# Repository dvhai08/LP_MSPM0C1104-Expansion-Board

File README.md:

# LP_MSPM0C1104-Expansion-Board
MSPM0C1104 LaunchPad™ development kit for 24-MHz Arm® Cortex®-M0+ MCU

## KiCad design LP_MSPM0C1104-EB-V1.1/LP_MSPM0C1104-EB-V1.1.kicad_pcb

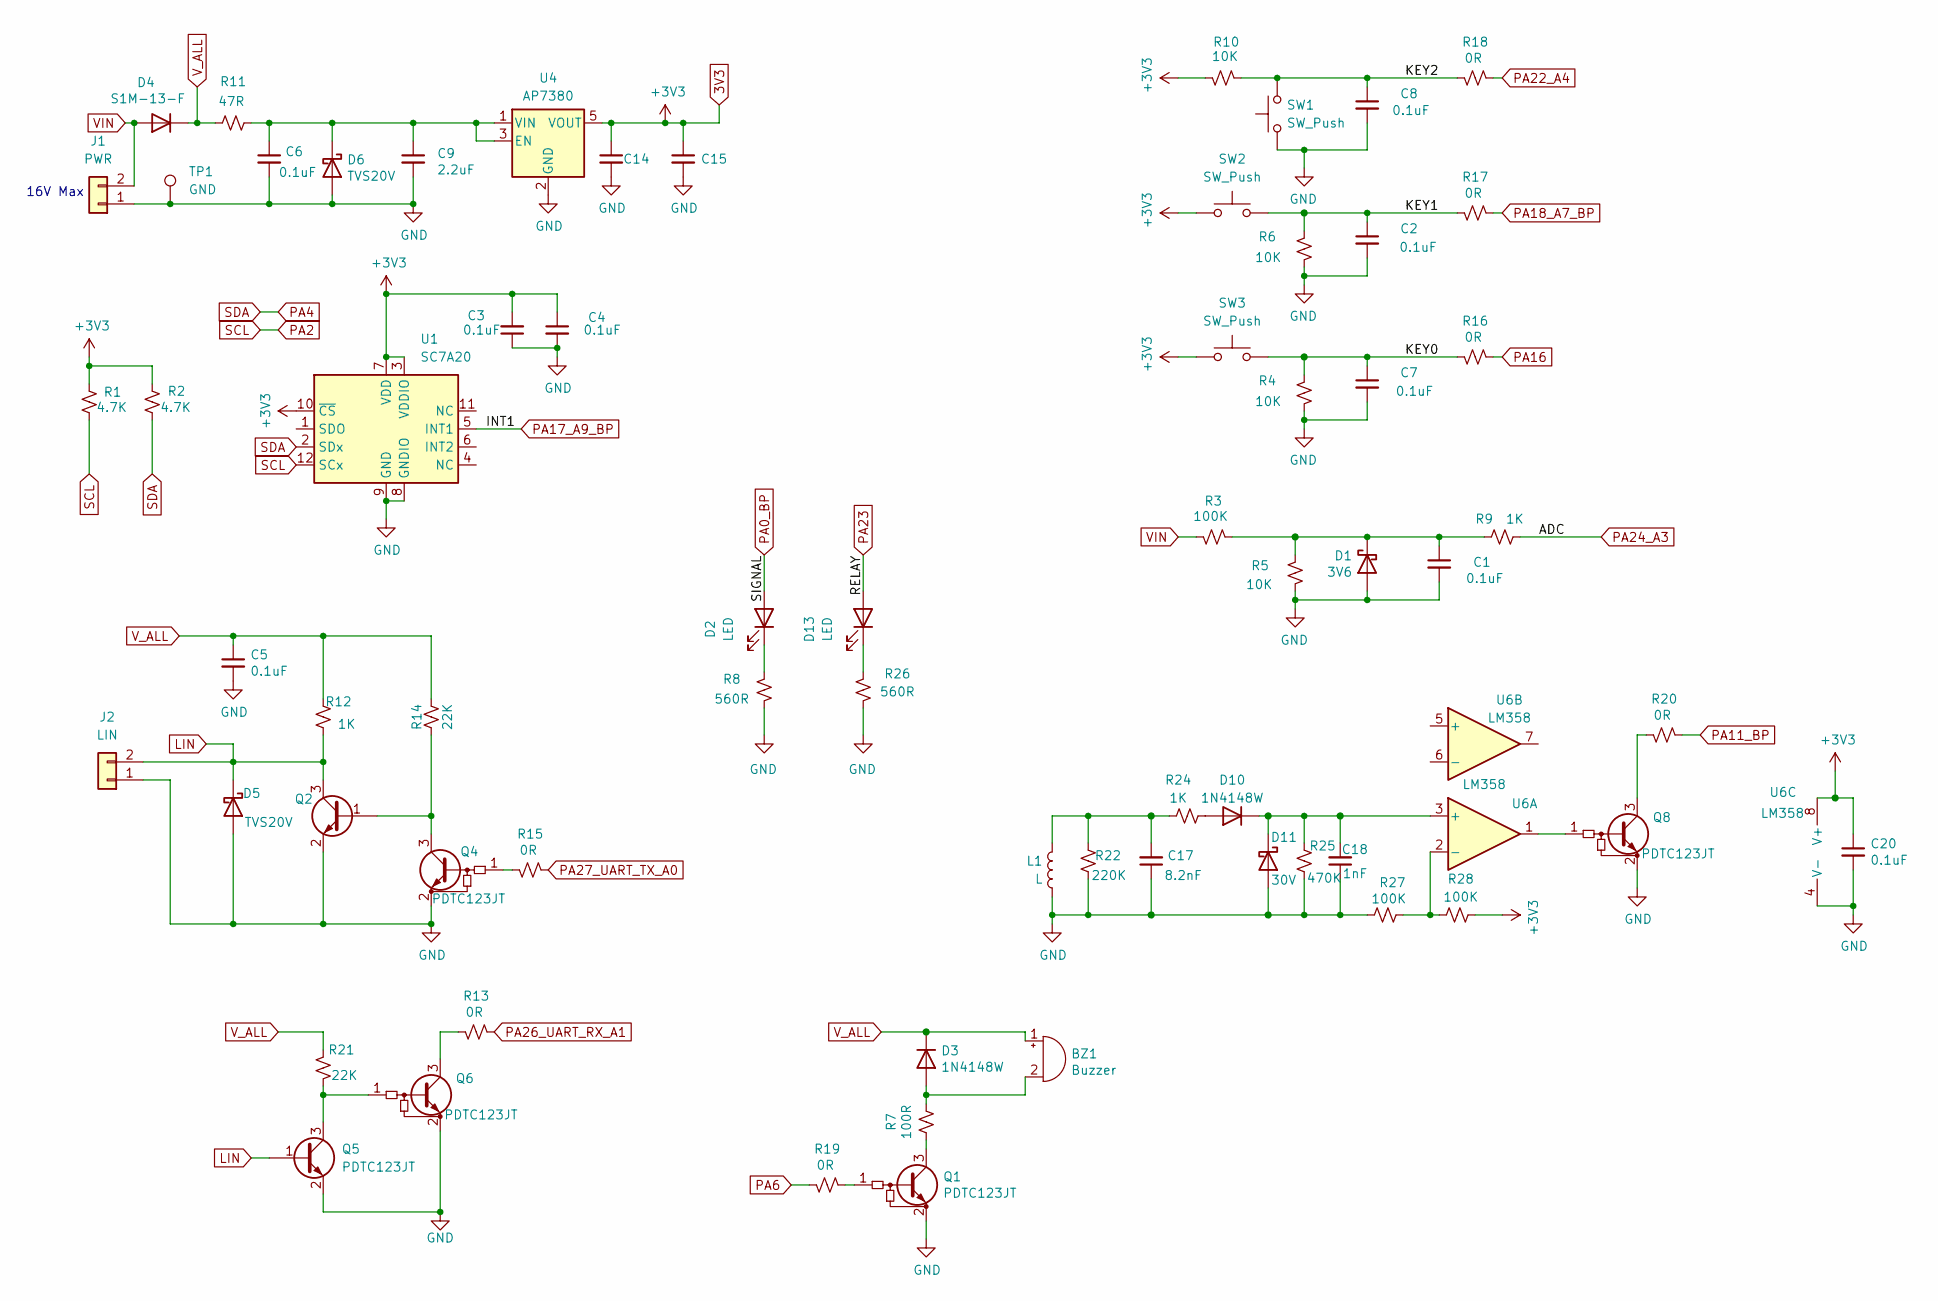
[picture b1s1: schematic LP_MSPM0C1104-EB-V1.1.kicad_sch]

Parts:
BZ1: Buzzer; BRT1209PF-06
C1, C2, C3, C4, C5, C6, C7, C8, C20: 0.1uF; C_0603_1608Metric
C9: 2.2uF; C_0603_1608Metric
C14: 0.1uF/50V; C_0402_1005Metric
C15: 4.7uF/10V; C_0603_1608Metric
C17: 8.2nF; C_0805_2012Metric
C18: 1nF; C_0603_1608Metric
D1: 3V6; D_SOD-323
D2, D13: LED; LED_0603_1608Metric
D3, D10: 1N4148W; D_SOD-123
D4: S1M-13-F; D_SMA
D5, D6: TVS20V; D_SMA
D11: 30V; D_SMA
J1: PWR; PinHeader_1x02_P2.54mm_Vertical
J2: LIN; PinHeader_1x02_P2.54mm_Vertical
L1: L; PinHeader_1x02_P2.54mm_Vertical
Q1, Q4, Q5, Q6, Q8: PDTC123JT; SOT-23
Q2: PBSS4041NT,215; SOT-23
R1, R2: 4.7K; R_0603_1608Metric
R3, R27, R28: 100K; R_0603_1608Metric
R4, R5, R6, R10: 10K; R_0603_1608Metric
R7: 100R; R_0805_2012Metric_Pad1.20x1.40mm_HandSolder
R8, R26: 560R; R_0603_1608Metric
R9, R24: 1K; R_0603_1608Metric
R11: 47R; R_1210_3225Metric
R12: 1K; R_1206_3216Metric
R13, R15, R16, R17, R18, R19, R20: 0R; R_0603_1608Metric
R14, R21: 22K; R_0603_1608Metric
R22: 220K; R_0603_1608Metric
R25: 470K; R_0603_1608Metric
SW1, SW2, SW3: SW_Push; SW_PUSH_6mm
TP1: GND; TestPoint_Pad_D1.0mm
U1: SC7A20; LGA-12_2x2mm_P0.5mm
U4: AP7380; SOT-23-5
U6: LM358; SOIC-8_3.9x4.9mm_P1.27mm

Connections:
3V3: C3.2, C4.1, C14.1, C15.1, C20.1, R1.1, R2.1, R10.1, R28.1, SW2.1, SW3.1, U1.3 (VDDIO), U1.7 (VDD), U1.10 (~CS), U4.5 (VOUT), U6.8 (V+); also elsewhere on the board
/KEY0: C7.1, R4.2, R16.2, SW3.2
/KEY1: C2.1, R6.2, R17.2, SW2.2
/KEY2: C8.1, R10.2, R18.2, SW1.2
GND: C1.2, C2.2, C3.1, C4.2, C5.2, C6.2, C7.2, C8.2, C9.2, C14.2, C15.2, C17.1, C18.1, C20.2, D1.2 (A), D5.2 (A), D6.2 (A), D11.2 (A), J1.1, J2.1, L1.2, Q1.2 (E), Q2.2 (E), Q4.2 (E), Q5.2 (E), Q6.2 (E), Q8.2 (E), R4.1, R5.1, R6.1, R8.1, R22.1, R25.1, R26.1, R27.1, SW1.1, TP1.1, U1.8 (GNDIO), U1.9 (GND), U4.2 (GND), U6.4 (V-); also elsewhere on the board
LIN: D5.1 (K), J2.2, Q2.3 (C), Q5.1 (B), R12.1
unnamed: BZ1.2 (+), D3.2 (A), R7.2
unnamed: C17.2, L1.1, R22.2, R24.2
unnamed: C1.1, D1.1 (K), R3.2, R5.2, R9.2
unnamed: D2.1 (K), R8.2
unnamed: C6.1, C9.1, D6.1 (K), R11.1, U4.1 (VIN), U4.3 (EN)
unnamed: D10.2 (A), R24.1
unnamed: C18.2, D10.1 (K), D11.1 (K), R25.2, U6.3 (+)
unnamed: D13.1 (K), R26.2
unnamed: Q1.1 (B), R19.1
unnamed: Q1.3 (C), R7.1
unnamed: Q2.1 (B), Q4.3 (C), R14.2
unnamed: Q4.1 (B), R15.2
unnamed: Q5.3 (C), Q6.1 (B), R21.1
unnamed: Q6.3 (C), R13.2
unnamed: Q8.1 (B), U6.1
unnamed: Q8.3 (C), R20.2
unnamed: R27.2, R28.2, U6.2 (-)
PA0_BP: D2.2 (A); also elsewhere on the board
PA2: R1.2, U1.12 (SCx); also elsewhere on the board
PA4: R2.2, U1.2 (SDx); also elsewhere on the board
PA6: R19.2; also elsewhere on the board
PA11_BP: R20.1; also elsewhere on the board
PA16: R16.1; also elsewhere on the board
PA17_A9_BP: U1.5 (INT1); also elsewhere on the board
PA18_A7_BP: R17.1; also elsewhere on the board
PA22_A4: R18.1; also elsewhere on the board
PA23: D13.2 (A); also elsewhere on the board
PA24_A3: R9.1; also elsewhere on the board
PA26_UART_RX_A1: R13.1; also elsewhere on the board
PA27_UART_TX_A0: R15.1; also elsewhere on the board
VIN: D4.2 (A), J1.2, R3.1
V_ALL: BZ1.1 (-), C5.1, D3.1 (K), D4.1 (K), R11.2, R12.2, R14.1, R21.2

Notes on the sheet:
16V Max

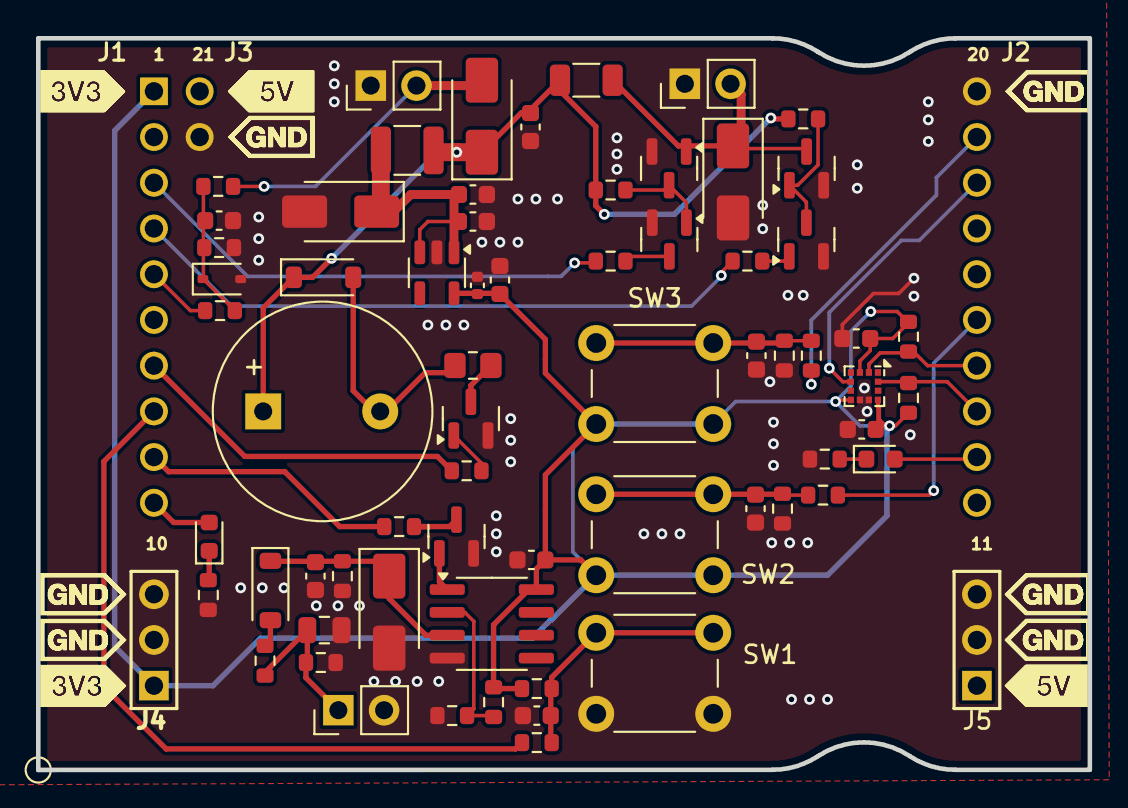
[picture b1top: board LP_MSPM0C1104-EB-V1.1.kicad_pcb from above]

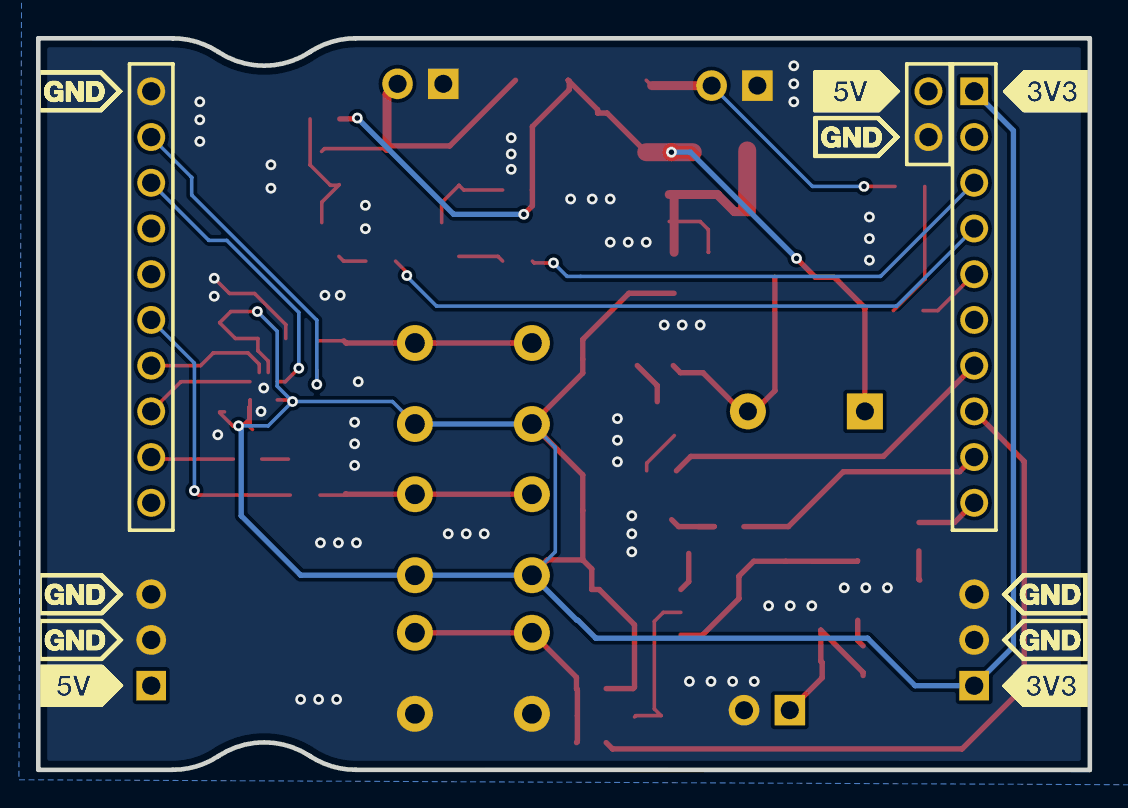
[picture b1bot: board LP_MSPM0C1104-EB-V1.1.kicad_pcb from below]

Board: 2 copper layers, 58.4 x 40.6 mm, 72 parts (3 on the bottom side), 39 nets.

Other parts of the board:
J1#2: SSQ-110-03-F-S; BoosterPack_20pin_J1
J2#2: SSQ-110-03-F-S; BoosterPack_20pin_J2
J3: SSQ-102-03-F-S; BoosterPack_20pin_J3
J4: PEC03SAAN; PEC03SAAN_Launchpad_3V3
J5: PEC03SAAN; PEC03SAAN_Launchpad_5V0

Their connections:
3V3: J1#2.1, J4.1; also elsewhere on the board
+5V: J3.21, J5.1
GND: J2#2.20, J3.22, J4.2, J4.3, J5.2, J5.3; also elsewhere on the board
PA0_BP: J1#2.10; also elsewhere on the board
PA2: J2#2.13; also elsewhere on the board
PA4: J2#2.14; also elsewhere on the board
PA6: J1#2.7; also elsewhere on the board
PA11_BP: J1#2.9; also elsewhere on the board
PA16: J2#2.19; also elsewhere on the board
PA17_A9_BP: J2#2.18; also elsewhere on the board
PA18_A7_BP: J2#2.15; also elsewhere on the board
PA22_A4: J1#2.8; also elsewhere on the board
PA23: J2#2.12; also elsewhere on the board
PA24_A3: J1#2.5; also elsewhere on the board
PA26_UART_RX_A1: J1#2.3; also elsewhere on the board
PA27_UART_TX_A0: J1#2.4; also elsewhere on the board

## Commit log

2025-05-24 3D view
2025-05-24 update value
2025-05-26 export gerber file
